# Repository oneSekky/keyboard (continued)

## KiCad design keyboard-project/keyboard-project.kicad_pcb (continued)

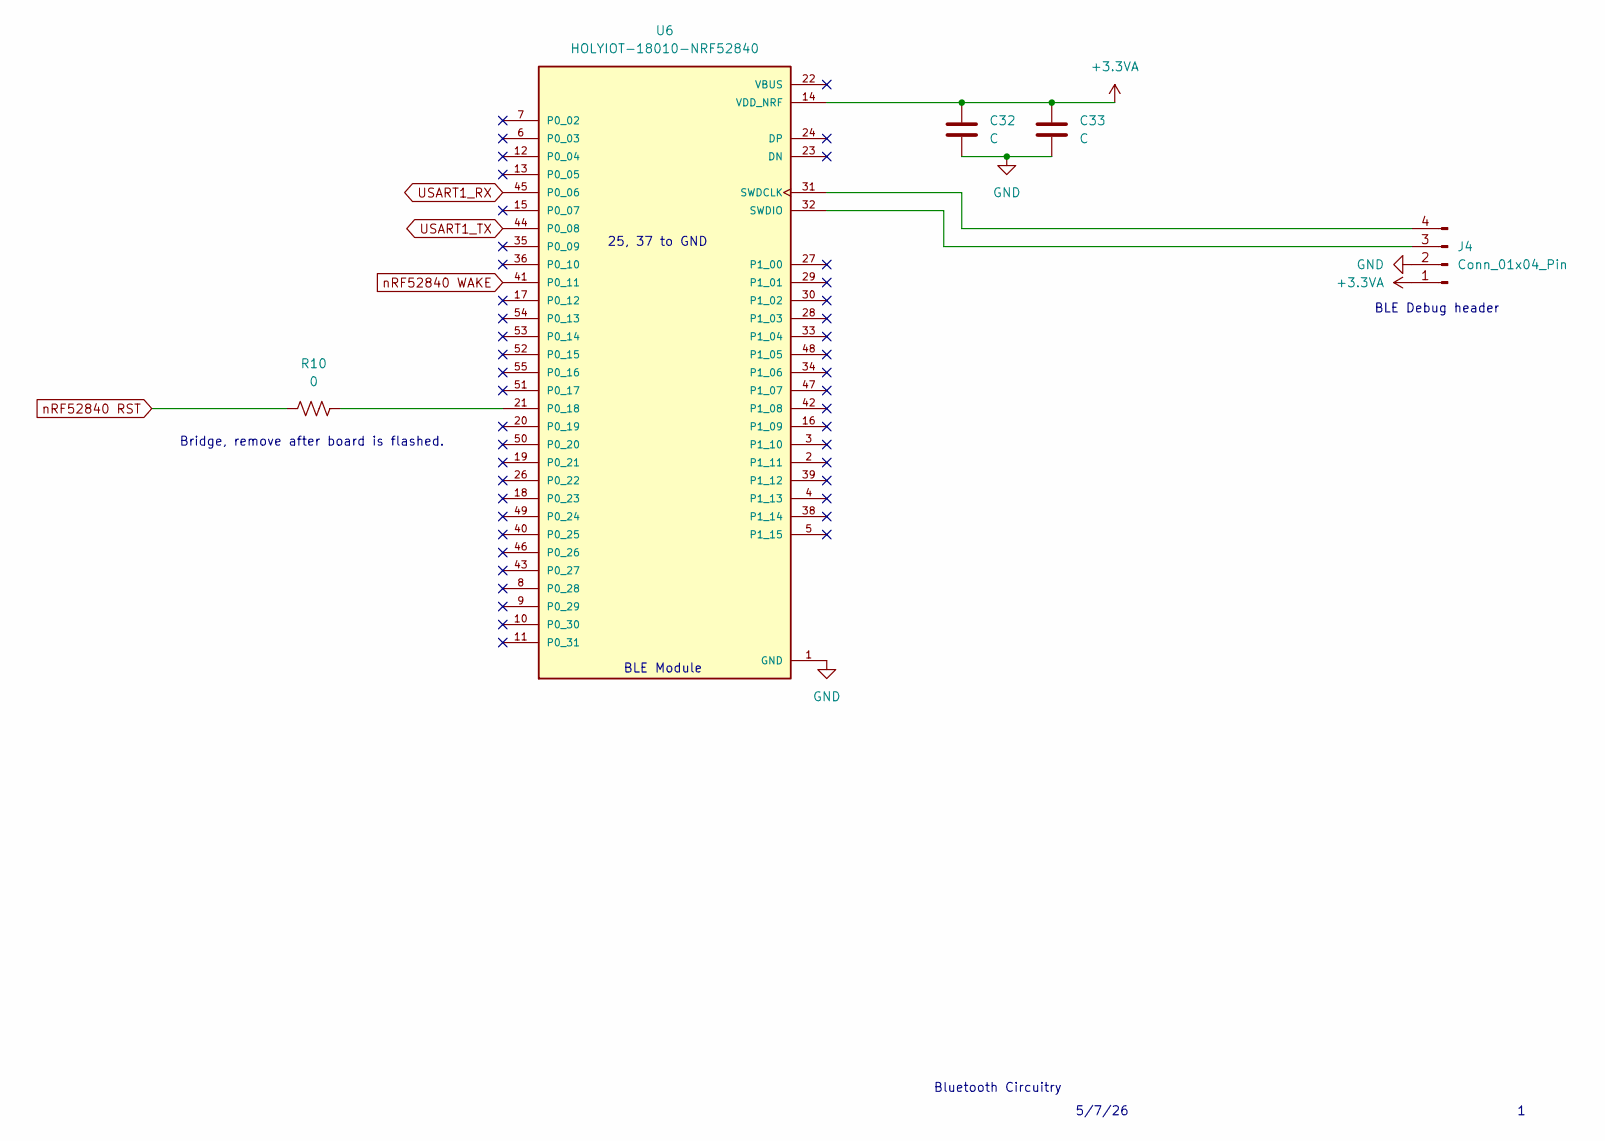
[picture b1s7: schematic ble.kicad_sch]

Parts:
C32, C33: C; C_1206_3216Metric_Pad1.33x1.80mm_HandSolder
J4: Conn_01x04_Pin; JST_EH_B4B-EH-A_1x04_P2.50mm_Vertical
R10: 0; R_1206_3216Metric_Pad1.30x1.75mm_HandSolder
U6: HOLYIOT-18010-NRF52840; XCVR_HOLYIOT-18010-NRF52840

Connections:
+3.3VA: C32.1, C33.1, J4.1, U6.14 (VDD_NRF); also elsewhere on the board
GND: C32.2, C33.2, J4.2, U6.1 (GND), U6.25 (GND), U6.37 (GND); also elsewhere on the board
unnamed: J4.3, U6.32 (SWDIO)
unnamed: J4.4, U6.31 (SWDCLK)
unnamed: R10.2, U6.21 (P0_18)
USART1_RX: U6.45 (P0_06); also elsewhere on the board
USART1_TX: U6.44 (P0_08); also elsewhere on the board
nRF52840 RST: R10.1; also elsewhere on the board
nRF52840 WAKE: U6.41 (P0_11); also elsewhere on the board

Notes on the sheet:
5/7/26
Bluetooth Circuitry
Bridge, remove after board is flashed.
BLE Module
25, 37 to GND
BLE Debug header

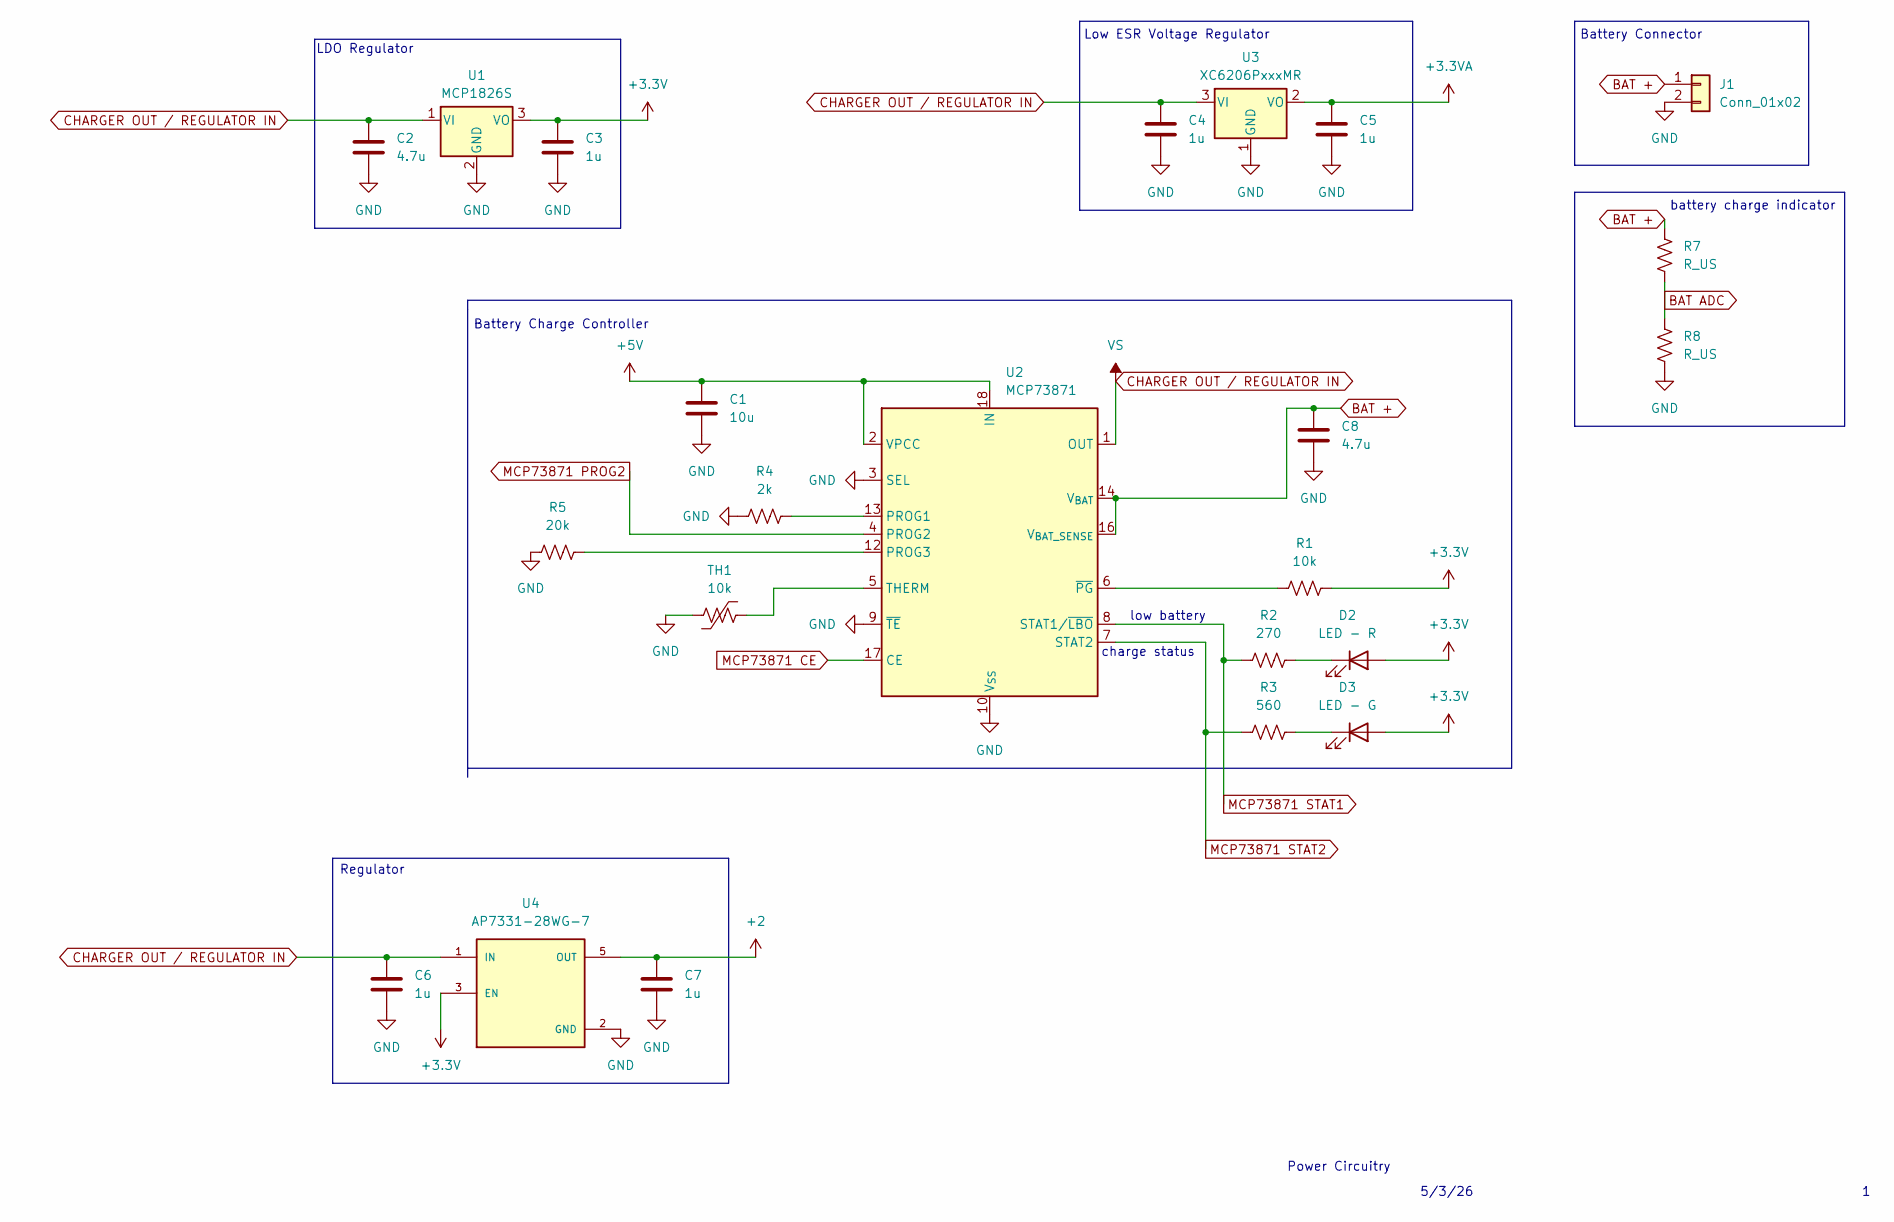
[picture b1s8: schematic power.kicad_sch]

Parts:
C1: 10u; C_1206_3216Metric_Pad1.33x1.80mm_HandSolder
C2, C8: 4.7u; C_1206_3216Metric_Pad1.33x1.80mm_HandSolder
C3, C4, C5, C6, C7: 1u; C_1206_3216Metric_Pad1.33x1.80mm_HandSolder
D2: LED - R; LED_1206_3216Metric
D3: LED - G; LED_1206_3216Metric
J1: Conn_01x02; JST_EH_B2B-EH-A_1x02_P2.50mm_Vertical
R1: 10k; R_1206_3216Metric_Pad1.30x1.75mm_HandSolder
R2: 270; R_1206_3216Metric_Pad1.30x1.75mm_HandSolder
R3: 560; R_1206_3216Metric_Pad1.30x1.75mm_HandSolder
R4: 2k; R_1206_3216Metric_Pad1.30x1.75mm_HandSolder
R5: 20k; R_1206_3216Metric_Pad1.30x1.75mm_HandSolder
R7, R8: R_US; R_1206_3216Metric_Pad1.30x1.75mm_HandSolder
TH1: 10k; R_01005_0402Metric
U1: MCP1826S; SOT230P700X180-4N
U2: MCP73871; QFN-20-1EP_4x4mm_P0.5mm_EP2.5x2.5mm
U3: XC6206PxxxMR; SOT-23-3
U4: AP7331-28WG-7; SOT95P285X145-5N; PART_REV 3-2

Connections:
+2: C7.1, U4.5 (OUT); also elsewhere on the board
+3.3V: C3.1, D2.2 (A), D3.2 (A), R1.2, U1.3 (VO), U4.3 (EN); also elsewhere on the board
+3.3VA: C5.1, U3.2 (VO); also elsewhere on the board
+5V: C1.1, U2.2 (VPCC), U2.18 (IN), U2.19 (IN); also elsewhere on the board
BAT +: C8.1, J1.1, R7.1, U2.14 (V_{BAT}), U2.15 (V_{BAT}), U2.16 (V_{BAT_SENSE})
BAT ADC: R7.2, R8.1; also elsewhere on the board
CHARGER OUT / REGULATOR IN: C2.1, C4.1, C6.1, U1.1 (VI), U2.1 (OUT), U2.20 (OUT), U3.3 (VI), U4.1 (IN); also elsewhere on the board
GND: C1.2, C2.2, C3.2, C4.2, C5.2, C6.2, C7.2, C8.2, J1.2, R4.1, R5.2, R8.2, TH1.2, U1.2 (GND), U2.3 (SEL), U2.9 (~TE), U2.10 (V_{SS}), U2.11 (V_{SS}), U2.21 (V_{SS}), U3.1 (GND), U4.2 (GND); also elsewhere on the board
MCP73871 CE: U2.17 (CE); also elsewhere on the board
MCP73871 PROG2: U2.4 (PROG2); also elsewhere on the board
MCP73871 STAT1: R2.1, U2.8 (STAT1/~LBO); also elsewhere on the board
MCP73871 STAT2: R3.1, U2.7 (STAT2); also elsewhere on the board
unnamed: D2.1 (K), R2.2
unnamed: D3.1 (K), R3.2
unnamed: R4.2, U2.13 (PROG1)
unnamed: R5.1, U2.12 (PROG3)
unnamed: TH1.1, U2.5 (THERM)
unnamed: R1.1, U2.6 (~PG)

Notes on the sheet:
charge status
5/3/26
Power Circuitry
battery charge indicator
Battery Charge Controller
Low ESR Voltage Regulator
low battery
LDO Regulator
Regulator
Battery Connector

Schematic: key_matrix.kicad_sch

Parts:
D1, D4, D5, D6, D7, D8, D9, D10, D11, D12, D13, D14, D15, D17, D18, D19, D20, D21, D22, D23, D24, D25, D26, D27, D28, D29, D30, D31, D32, D33, D34, D35, D36, D37, D38, D39, D40, D41, D42, D43, D44, D45, D46, D47, D48, D49, D50, D51, D52, D53, D54, D55, D56, D57, D58, D59, D60, D61, D62, D63, D65, D67, D69, D71, D72, D73, D74, D75, D76, D77, D79, D81, D82, D83, D85, D87, D88, D89, D90, D91, D92, D93, D94, D95, D96, D97, D98, D99, D100: 1N4148W; D_SOD-123
SW1, SW2, SW3, SW4, SW5, SW6, SW7, SW8, SW9, SW10, SW11, SW12, SW13, SW14, SW15, SW16, SW17, SW18, SW19, SW20, SW21, SW22, SW23, SW24, SW25, SW26, SW27, SW28, SW29, SW31, SW32, SW33, SW34, SW35, SW36, SW37, SW38, SW39, SW40, SW41, SW42, SW43, SW44, SW45, SW46, SW47, SW48, SW51, SW52, SW53, SW54, SW55, SW56, SW57, SW58, SW59, SW60, SW61, SW65, SW66, SW67, SW68, SW69, SW70, SW71, SW72, SW73, SW74, SW76, SW77, SW78, SW79, SW88, SW89: SW_Push; SW_Cherry_MX_1.00u_PCB
SW30: SW_Push; SW_Cherry_MX_2.00u_PCB
SW49, SW50: SW_Push; SW_Cherry_MX_1.50u_PCB
SW62, SW64: SW_Push; SW_Cherry_MX_2.25u_PCB
SW63: SW_Push; SW_Cherry_MX_1.75u_PCB
SW75: SW_Push; SW_Cherry_MX_2.75u_PCB
SW80, SW81, SW82, SW83, SW84, SW85, SW86: SW_Push; SW_Cherry_MX_1.25u_PCB
SW87: SW_Push; SW_Cherry_MX_6.25u_PCB

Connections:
Matrix Col 0: SW1.2, SW17.2, SW50.2, SW63.2, SW64.2, SW80.2; also elsewhere on the board
Matrix Col 1: SW2.2, SW18.2, SW34.2, SW51.2, SW65.2, SW81.2; also elsewhere on the board
Matrix Col 2: SW3.2, SW19.2, SW35.2, SW52.2, SW66.2, SW82.2; also elsewhere on the board
Matrix Col 3: SW4.2, SW20.2, SW36.2, SW53.2, SW67.2; also elsewhere on the board
Matrix Col 4: SW5.2, SW21.2, SW37.2, SW54.2, SW68.2; also elsewhere on the board
Matrix Col 5: SW6.2, SW22.2, SW38.2, SW55.2, SW69.2, SW87.2; also elsewhere on the board
Matrix Col 6: SW7.2, SW23.2, SW39.2, SW56.2, SW70.2; also elsewhere on the board
Matrix Col 7: SW8.2, SW24.2, SW40.2, SW57.2, SW71.2; also elsewhere on the board
Matrix Col 8: SW9.2, SW25.2, SW41.2, SW58.2, SW72.2, SW83.2; also elsewhere on the board
Matrix Col 9: SW10.2, SW26.2, SW42.2, SW59.2, SW73.2, SW84.2; also elsewhere on the board
Matrix Col 10: SW11.2, SW27.2, SW43.2, SW60.2, SW74.2, SW85.2; also elsewhere on the board
Matrix Col 11: SW12.2, SW28.2, SW44.2, SW61.2, SW75.2, SW86.2; also elsewhere on the board
Matrix Col 12: SW13.2, SW29.2, SW45.2, SW62.2; also elsewhere on the board
Matrix Col 13: SW30.2, SW49.2, SW76.2; also elsewhere on the board
Matrix Col 14: SW14.2, SW31.2, SW46.2, SW77.2; also elsewhere on the board
Matrix Col 15: SW15.2, SW32.2, SW47.2, SW78.2; also elsewhere on the board
Matrix Col 16: SW16.2, SW33.2, SW48.2, SW79.2; also elsewhere on the board
Matrix Row 0: D1.1 (K), D4.1 (K), D5.1 (K), D6.1 (K), D7.1 (K), D8.1 (K), D9.1 (K), D10.1 (K), D11.1 (K), D12.1 (K), D13.1 (K), D14.1 (K), D15.1 (K), D17.1 (K), D18.1 (K), D19.1 (K); also elsewhere on the board
Matrix Row 1: D20.1 (K), D21.1 (K), D22.1 (K), D23.1 (K), D24.1 (K), D25.1 (K), D26.1 (K), D27.1 (K), D28.1 (K), D29.1 (K), D30.1 (K), D31.1 (K), D32.1 (K), D33.1 (K), D34.1 (K), D35.1 (K), D36.1 (K); also elsewhere on the board
Matrix Row 2: D37.1 (K), D39.1 (K), D41.1 (K), D43.1 (K), D45.1 (K), D47.1 (K), D49.1 (K), D51.1 (K), D53.1 (K), D55.1 (K), D57.1 (K), D59.1 (K), D61.1 (K), D63.1 (K), D65.1 (K), D67.1 (K), D69.1 (K); also elsewhere on the board
Matrix Row 3: D38.1 (K), D40.1 (K), D42.1 (K), D44.1 (K), D46.1 (K), D48.1 (K), D50.1 (K), D52.1 (K), D54.1 (K), D56.1 (K), D58.1 (K), D60.1 (K), D62.1 (K); also elsewhere on the board
Matrix Row 4: D71.1 (K), D73.1 (K), D75.1 (K), D77.1 (K), D79.1 (K), D81.1 (K), D83.1 (K), D85.1 (K), D87.1 (K), D89.1 (K), D91.1 (K), D93.1 (K), D95.1 (K); also elsewhere on the board
Matrix Row 5: D72.1 (K), D74.1 (K), D76.1 (K), D82.1 (K), D88.1 (K), D90.1 (K), D92.1 (K), D94.1 (K), D96.1 (K), D97.1 (K), D98.1 (K), D99.1 (K), D100.1 (K); also elsewhere on the board
unnamed: D1.2 (A), SW1.1
unnamed: D4.2 (A), SW2.1
unnamed: D5.2 (A), SW3.1
unnamed: D6.2 (A), SW4.1
unnamed: D7.2 (A), SW5.1
unnamed: D8.2 (A), SW6.1
unnamed: D9.2 (A), SW7.1
unnamed: D10.2 (A), SW8.1
unnamed: D11.2 (A), SW9.1
unnamed: D12.2 (A), SW10.1
unnamed: D13.2 (A), SW11.1
unnamed: D14.2 (A), SW12.1
unnamed: D15.2 (A), SW13.1
unnamed: D17.2 (A), SW14.1
unnamed: D18.2 (A), SW15.1
unnamed: D19.2 (A), SW16.1
unnamed: D20.2 (A), SW17.1
unnamed: D21.2 (A), SW18.1
unnamed: D22.2 (A), SW19.1
unnamed: D23.2 (A), SW20.1
unnamed: D24.2 (A), SW21.1
unnamed: D25.2 (A), SW22.1
unnamed: D26.2 (A), SW23.1
unnamed: D27.2 (A), SW24.1
unnamed: D28.2 (A), SW25.1
unnamed: D29.2 (A), SW26.1
unnamed: D30.2 (A), SW27.1
unnamed: D31.2 (A), SW28.1
unnamed: D32.2 (A), SW29.1
unnamed: D33.2 (A), SW30.1
unnamed: D34.2 (A), SW31.1
unnamed: D35.2 (A), SW32.1
unnamed: D36.2 (A), SW33.1
unnamed: D37.2 (A), SW50.1
unnamed: D38.2 (A), SW63.1
unnamed: D39.2 (A), SW34.1
unnamed: D40.2 (A), SW51.1
unnamed: D41.2 (A), SW35.1
unnamed: D42.2 (A), SW52.1
unnamed: D43.2 (A), SW36.1
unnamed: D44.2 (A), SW53.1
unnamed: D45.2 (A), SW37.1
unnamed: D46.2 (A), SW54.1
unnamed: D47.2 (A), SW38.1
unnamed: D48.2 (A), SW55.1
unnamed: D49.2 (A), SW39.1
unnamed: D50.2 (A), SW56.1
unnamed: D51.2 (A), SW40.1
unnamed: D52.2 (A), SW57.1
unnamed: D53.2 (A), SW41.1
unnamed: D54.2 (A), SW58.1
unnamed: D55.2 (A), SW42.1
unnamed: D56.2 (A), SW59.1
unnamed: D57.2 (A), SW43.1
unnamed: D58.2 (A), SW60.1
unnamed: D59.2 (A), SW44.1
unnamed: D60.2 (A), SW61.1
unnamed: D61.2 (A), SW45.1
unnamed: D62.2 (A), SW62.1
unnamed: D63.2 (A), SW49.1
unnamed: D65.2 (A), SW46.1
unnamed: D67.2 (A), SW47.1
unnamed: D69.2 (A), SW48.1
unnamed: D71.2 (A), SW64.1
unnamed: D72.2 (A), SW80.1
unnamed: D73.2 (A), SW65.1
unnamed: D74.2 (A), SW81.1
unnamed: D75.2 (A), SW66.1
unnamed: D76.2 (A), SW82.1
unnamed: D77.2 (A), SW67.1
unnamed: D79.2 (A), SW68.1
unnamed: D81.2 (A), SW69.1
unnamed: D82.2 (A), SW87.1
unnamed: D83.2 (A), SW70.1
unnamed: D85.2 (A), SW71.1
unnamed: D87.2 (A), SW72.1
unnamed: D88.2 (A), SW83.1
unnamed: D89.2 (A), SW73.1
unnamed: D90.2 (A), SW84.1
unnamed: D91.2 (A), SW74.1
unnamed: D92.2 (A), SW85.1
unnamed: D93.2 (A), SW75.1
unnamed: D94.2 (A), SW86.1
unnamed: D95.2 (A), SW76.1
unnamed: D96.2 (A), SW88.1 (1_1)
unnamed: D97.2 (A), SW89.1 (1_1)
unnamed: D98.2 (A), SW77.1
unnamed: D99.2 (A), SW78.1
unnamed: D100.2 (A), SW79.1

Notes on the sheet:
R-Click
L Win
Down Arrow
Space
Pause/Break
Print Screen
F12
Ins
R Win
L Ctrl
Del
Scroll Lck
Right Arrow
Keyboard Key Matrix Circuitry
R Ctrl
Left Arrow
Page Down
F11
L-Click
Home
End
L Alt
R Shift
Tab
Context
ESC
Enter
5/7/26
F10
Up Arrow
R Alt
Caps Lck
L Shift
Page Up
Backspace

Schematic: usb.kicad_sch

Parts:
C31: 100n; C_1206_3216Metric_Pad1.33x1.80mm_HandSolder
FB1, FB2: 600 @ 100MHz; L_Walsin_WLFM201209x
J3: USB_C_Receptacle; USB_C_Receptacle_GCT_USB4105-xx-A_16P_TopMnt_Horizontal
R6, R9: 5.1k; R_1206_3216Metric_Pad1.30x1.75mm_HandSolder
R13, R14: R_US; R_1206_3216Metric_Pad1.30x1.75mm_HandSolder

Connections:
+5V: C31.2, J3.A4 (VBUS), J3.A9 (VBUS), J3.B4 (VBUS), J3.B9 (VBUS), R13.1; also elsewhere on the board
GND: C31.1, J3.A1 (GND), J3.A12 (GND), J3.B1 (GND), J3.B12 (GND), J3.SH (SHIELD), R6.2, R9.2, R14.2; also elsewhere on the board
unnamed: FB1.1, J3.A7 (D-), J3.B7 (D-)
unnamed: FB2.1, J3.A6 (D+), J3.B6 (D+)
unnamed: J3.A5 (CC1), R6.1
unnamed: J3.B5 (CC2), R9.1
USB D+: FB2.2; also elsewhere on the board
USB D-: FB1.2; also elsewhere on the board
VBUS Detect: R13.2, R14.1; also elsewhere on the board

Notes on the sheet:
VBUS detection on the MCU, should ouput 2V5 when USB is plugged in
USB Circuitry
5/3/26

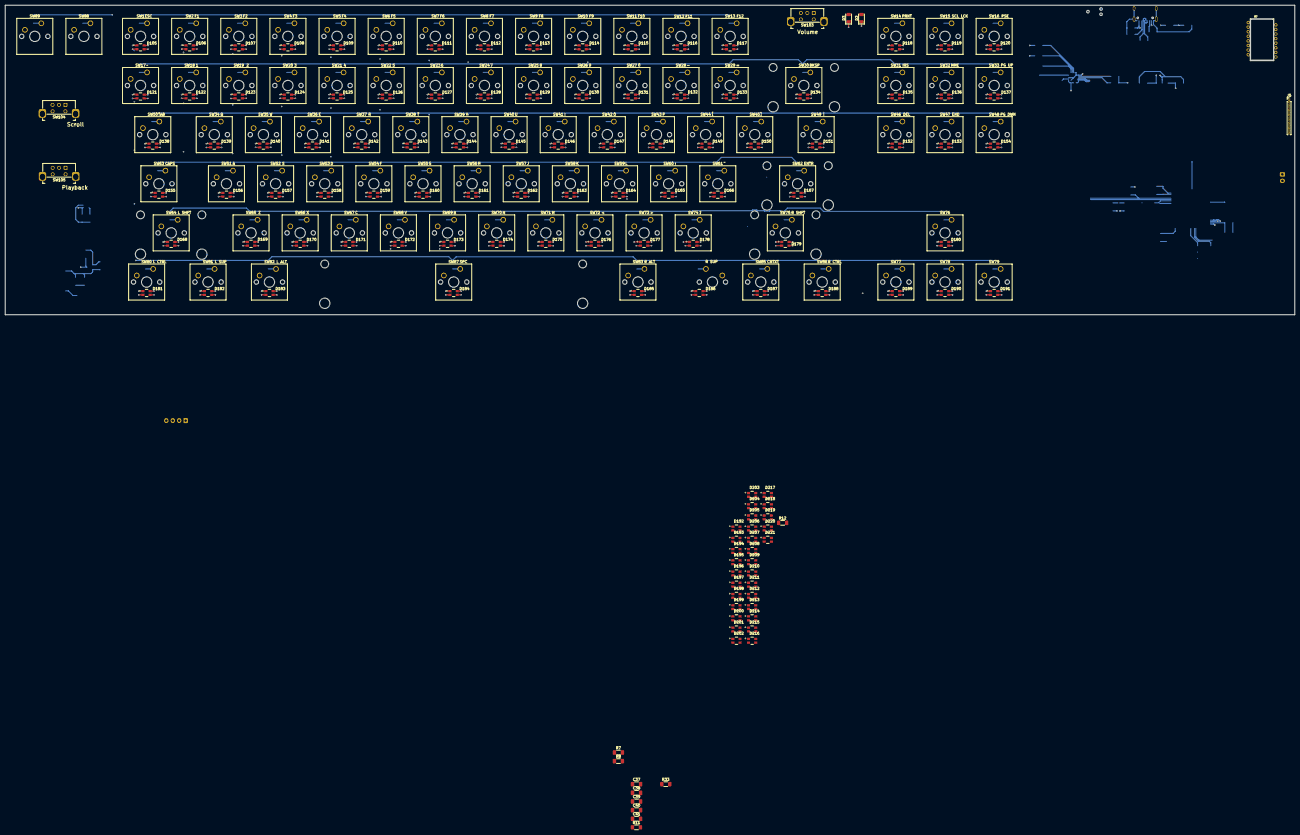
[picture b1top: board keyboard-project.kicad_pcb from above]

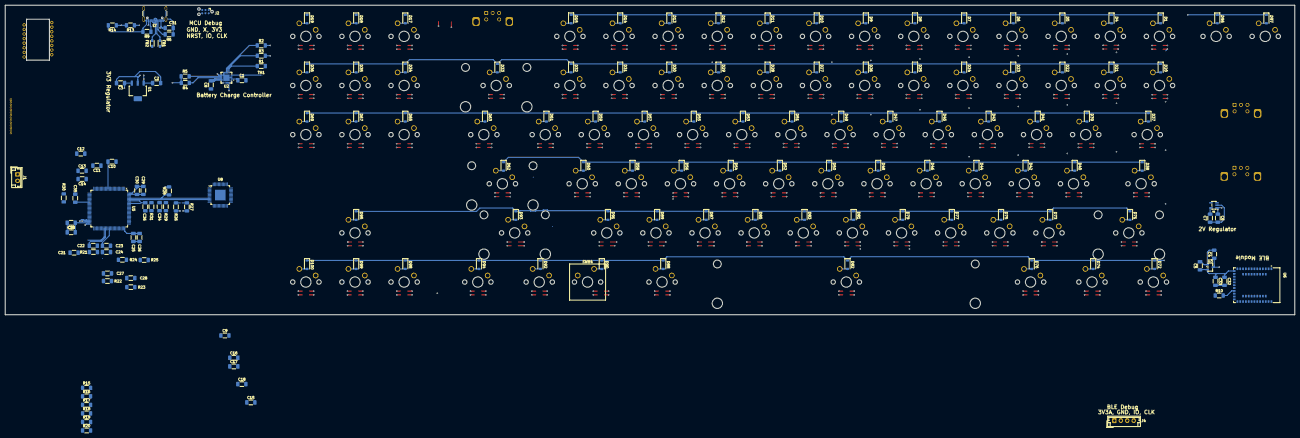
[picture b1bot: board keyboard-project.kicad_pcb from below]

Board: 8 copper layers, 500.0 x 120.0 mm, 389 parts (167 on the bottom side), 230 nets.

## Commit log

2026-05-03 Add initial KiCad project files
2026-05-03 Create sheets for each subsystem
2026-05-03 working on power
2026-05-03 power circuitry manufacturer suggested schematics and kicad footprint folder
2026-05-08 ble update
2026-05-08 some keyboard
2026-05-14 encoders, trackball, and display circuits
2026-05-18 led page
2026-05-26 res and cap footprints
2026-05-26 more footprints
2026-05-26 all footprints in now
2026-05-26 working on pcb layout, power
2026-05-28 pcb layout - keys and diodes
2026-05-28 pcb layout, leds for keycaps
2026-05-29 more layout, all keycaps/leds are routed, need to place ICs now
2026-06-03 resistors and caps for mcu
